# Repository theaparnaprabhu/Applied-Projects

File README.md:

# Applied-Projects
Applied, hands-on projects that go beyond quick learning exercises — real builds combining hardware, firmware, and design.
This repo houses my mid-scale, hands-on projects — things that started as learning exercises 
but grew into complete, working builds. Unlike my Minor Projects repo (quick 
experiments and learning snippets), these projects involve full design cycles: schematic, PCB 
layout, firmware, and testing.

## What's Here

Each folder is a self-contained project with its own README, schematics/PCB files, source code, 
and notes on what I learned.

| Project | Description | Tech Stack |
|---|---|---|
| Smart Office Automation PCB| Custom PCB for automating office lighting, temperature, and occupancy sensing | KiCad, ESP32, C/C++ |
| ... | ... | ... |

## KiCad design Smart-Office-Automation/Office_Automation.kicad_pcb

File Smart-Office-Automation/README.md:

# Smart Office Automation PCB

A custom ESP32-based PCB that automates office environment control — lighting, temperature 
monitoring, and occupancy detection — with a web dashboard for real-time monitoring and control.

## Features

- **Occupancy Detection** — Automatically detects when the office is in use (e.g. via PIR/motion sensor)
- **Lighting Control** — Automatically switches lighting based on occupancy and/or ambient light levels using LDR
- **Temperature Monitoring** — Reads and logs ambient temperature in real time using DHT11 sensor
- **Web Dashboard** — Live monitoring and manual override via a browser-based interface
- **ESP32-Powered** — Wi-Fi enabled, no external gateway or hub required

## Hardware

| Component | Details |
|---|---|
| MCU | ESP32 |
| Sensors | Temperature sensor, occupancy/PIR sensor |
| Actuators | Relay/MOSFET-driven lighting output |
| PCB Design Tool | KiCad |

## Firmware

Written in C/C++ using the Arduino/ESP-IDF framework. Handles:
- Sensor polling (temperature, occupancy)
- Lighting control logic
- Wi-Fi connectivity and web server hosting for the dashboard

## Web Dashboard

The ESP32 hosts a lightweight web dashboard accessible over the local network, showing:
- Current temperature
- Occupancy status (occupied / vacant)
- Lighting state (on/off, and manual override toggle)

## Getting Started

### Hardware Setup
1. Fabricate the PCB using the files provided
2. Solder components per the BOM
3. Power the board via [power source]

### Accessing the Dashboard
1. After flashing and powering on, the ESP32 starts broadcasting a Wi-Fi network
2. On your phone or laptop, connect to this Wi-Fi network
3. Open a browser and navigate to the ESP32's AP IP address (default: `192.168.4.1`)
4. The dashboard loads, showing live sensor data and controls
5. Options for Auto mode and Manual mode are provided in the dashboard for efficient functioning

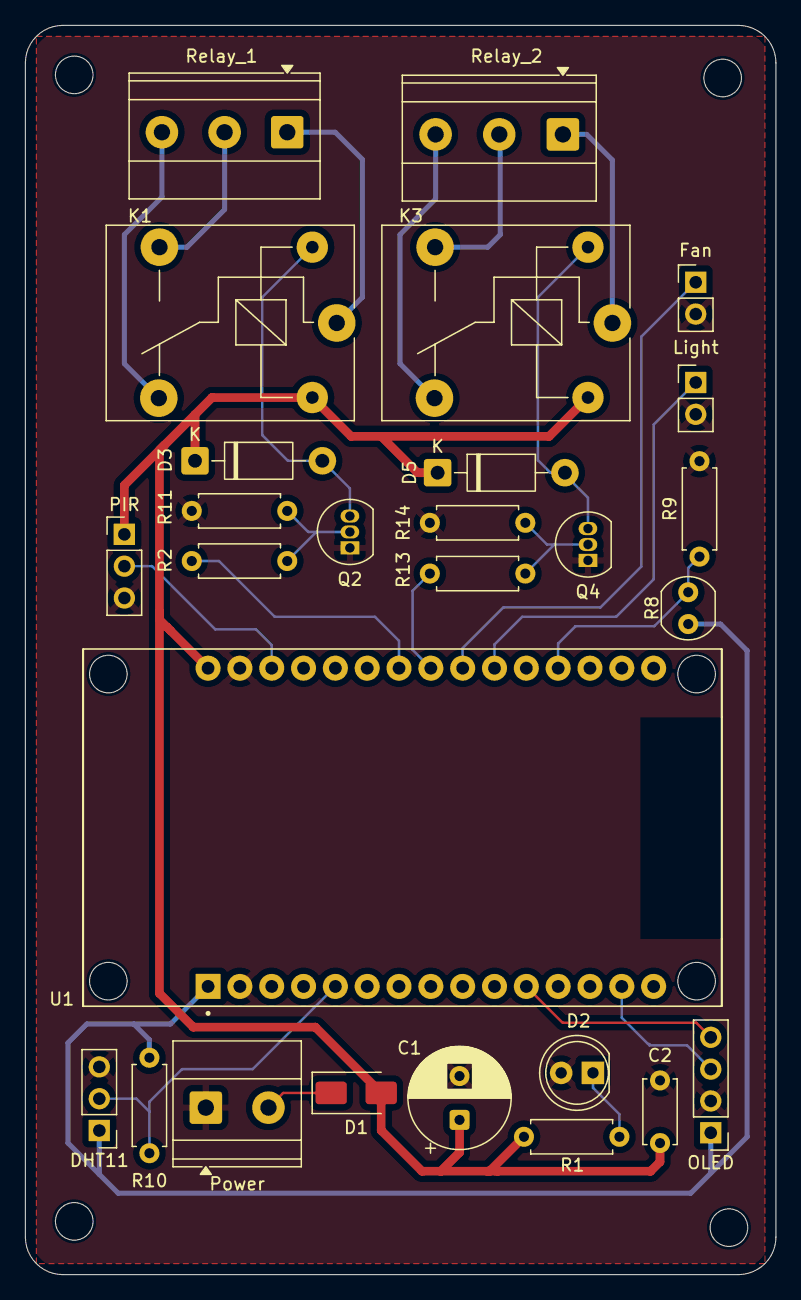
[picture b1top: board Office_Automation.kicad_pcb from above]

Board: 2 copper layers, 59.9 x 99.7 mm, 27 parts (0 on the bottom side), 24 nets.

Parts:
C1: 100uF 25V; CP_Radial_D8.0mm_P3.50mm
C2: 100nF 50V; C_Disc_D5.0mm_W2.5mm_P5.00mm
D1: SS14; D_SMA
D2: PWR_LED; LED_D5.0mm
D3, D5: 1N4007; D_DO-41_SOD81_P10.16mm_Horizontal
DHT11: DHT11; PinHeader_1x03_P2.54mm_Vertical
Fan: FAN_BTN; PinHeader_1x02_P2.54mm_Vertical
K1, K3: SANYOU_SRD_Form_C; Relay_SPDT_SANYOU_SRD_Series_Form_C
Light: LIGHT_BTN; PinHeader_1x02_P2.54mm_Vertical
OLED: OLED; PinHeader_1x04_P2.54mm_Vertical
PIR: PIR; PinHeader_1x03_P2.54mm_Vertical
Power: Power; TerminalBlock_Phoenix_MKDS-1,5-2_1x02_P5.00mm_Horizontal
Q2, Q4: PN2222A; TO-92_Inline
R1: 470; R_Axial_DIN0207_L6.3mm_D2.5mm_P7.62mm_Horizontal
R2, R13: 1k; R_Axial_DIN0207_L6.3mm_D2.5mm_P7.62mm_Horizontal
R8: R_Photo; R_LDR_4.9x4.2mm_P2.54mm_Vertical
R9, R10: 10k; R_Axial_DIN0207_L6.3mm_D2.5mm_P7.62mm_Horizontal
R11, R14: 100k; R_Axial_DIN0207_L6.3mm_D2.5mm_P7.62mm_Horizontal
Relay_1: Relay1; TerminalBlock_Phoenix_MKDS-1,5-3_1x03_P5.00mm_Horizontal
Relay_2: Relay2; TerminalBlock_Phoenix_MKDS-1,5-3-5.08_1x03_P5.08mm_Horizont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
U1: ESP32-DEVKIT-V1; MODULE_ESP32_DEVKIT_V1

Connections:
+3.3V: DHT11.1, OLED.1, R8.1, R10.1, U1.1 (3V3)
+5V: C1.1, C2.1, D1.2 (A), D3.1 (K), D5.1 (K), K1.5, K3.5, PIR.1, R1.1, U1.30 (VIN)
DHT_DATA: DHT11.2, R10.2, U1.5 (D4)
FAN_BTN: Fan.1, U1.22 (D33)
GND: C1.2, C2.2, D2.2 (A), DHT11.3, Fan.2, Light.2, OLED.2, PIR.3, Power.1, Q2.1 (E), Q4.1 (E), R9.2, R11.1, R14.1, U1.2 (GND), U1.29 (GND)
LDR_ADC: R8.2, R9.1, U1.19 (D34)
LIGHT_BTN: Light.1, U1.21 (D32)
unnamed: D1.1 (K), Power.2
unnamed: D2.1 (K), R1.2
unnamed: D3.2 (A), K1.2, Q2.3 (C)
unnamed: D5.2 (A), K3.2, Q4.3 (C)
unnamed: K1.1, Relay_1.1
unnamed: K1.3, Relay_1.2
unnamed: K1.4, Relay_1.3
unnamed: K3.1, Relay_2.1
unnamed: K3.3, Relay_2.2
unnamed: K3.4, Relay_2.3
unnamed: Q2.2 (B), R2.2, R11.2
unnamed: Q4.2 (B), R13.2, R14.2
PIR_OUT: PIR.2, U1.28 (D13)
RELAY1: R2.1, U1.24 (D26)
RELAY2: R13.1, U1.23 (D25)
SCL: OLED.3, U1.14 (D22)
SDA: OLED.4, U1.11 (D21)

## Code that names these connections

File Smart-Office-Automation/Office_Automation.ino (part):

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    GPIO4   -> DHT11 data           (J12)
    GPIO21  -> I2C SDA              (OLED, J4)
    GPIO22  -> I2C SCL              (OLED, J4)
    GPIO34  -> LDR_ADC (analog in)  (R8/R9 divider)
    GPIO32  -> LIGHT_BTN            (J7, active LOW w/ internal pullup)
    GPIO33  -> FAN_BTN              (J8, active LOW w/ internal pullup)
    GPIO26  -> RELAY1 -> Q2 -> K1 -> J9   = FAN
    GPIO25  -> RELAY2 -> Q4 -> K3 -> J13  = LIGHT
    GPIO13  -> PIR_OUT               (J3, active HIGH on motion)
  ============================================================================
*/

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#define PIN_SDA        21
#define PIN_SCL        22
#define PIN_LDR        34
#define PIN_LIGHT_BTN  32
#define PIN_FAN_BTN    33
#define PIN_RELAY_FAN  26
#define PIN_RELAY_LIGHT 25
#define PIN_PIR        13
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void setup() {
  Serial.begin(115200);

  pinMode(PIN_LIGHT_BTN, INPUT_PULLUP);
  pinMode(PIN_FAN_BTN, INPUT_PULLUP);
  pinMode(PIN_PIR, INPUT);
  pinMode(PIN_RELAY_FAN, OUTPUT);
  pinMode(PIN_RELAY_LIGHT, OUTPUT);
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void loop() {
  readSensors();

  bool lightReading = debouncedRead(PIN_LIGHT_BTN, lightRawLast, lightDebounceMs, lightBtnLast);
  bool fanReading   = debouncedRead(PIN_FAN_BTN, fanRawLast, fanDebounceMs, fanBtnLast);

  handleButton(lightReading, lightPrevStable, lightBtnDownMs, lightLongHandled, lightMode, lightState, setLight);
  handleButton(fanReading, fanPrevStable, fanBtnDownMs, fanLongHandled, fanMode, fanState, setFan);
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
